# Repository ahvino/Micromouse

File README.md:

# Micromouse
Team Pizza's Micromouse
This is Team pizza's Micromouse...

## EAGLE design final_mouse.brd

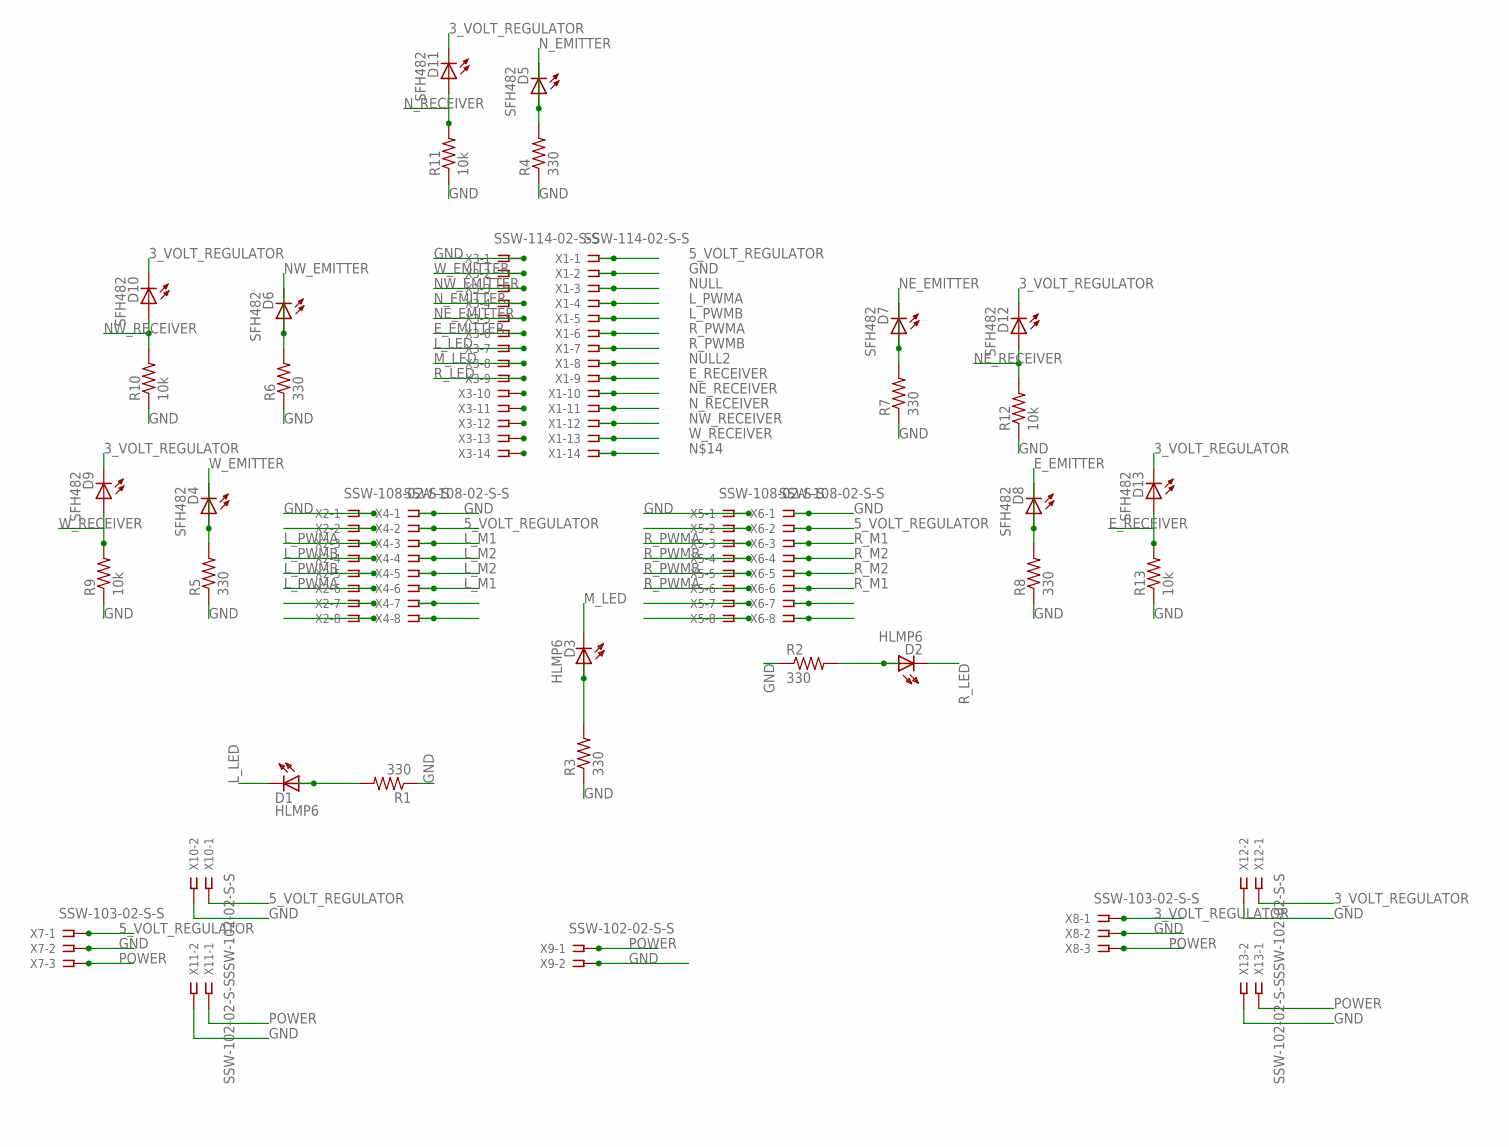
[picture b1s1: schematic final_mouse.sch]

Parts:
D1, D2, D3: HLMP6
D4, D5, D6, D7, D8, D9, D10, D11, D12, D13: SFH482
R1, R2, R3, R4, R5, R6, R7, R8: 330; 0204V
R9, R10, R11, R12, R13: 10k; 0204V
X1, X3: SSW-114-02-S-S
X2, X4, X5, X6: SSW-108-02-S-S
X7, X8: SSW-103-02-S-S
X9, X10, X11, X12, X13: SSW-102-02-S-S

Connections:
3_VOLT_REGULATOR: D9.K (C), D10.K (C), D11.K (C), D12.K (C), D13.K (C), X8.1, X12.1
5_VOLT_REGULATOR: X1.1, X4.2, X6.2, X7.1, X10.1
E_EMITTER: D8.A, D8.K (C), R8.2, X3.6
E_RECEIVER: D13.A, R13.2, X1.9
GND: R1.1, R2.1, R3.1, R4.1, R5.1, R6.1, R7.1, R8.1, R9.1, R10.1, R11.1, R12.1, R13.1, X1.2, X2.1, X3.1, X4.1, X5.1, X6.1, X7.2, X8.2, X9.2, X10.2, X11.2, X12.2, X13.2
L_LED: D1.K, X3.7
L_M1: X4.3, X4.6
L_M2: X4.4, X4.5
L_PWMA: X1.4, X2.3, X2.6
L_PWMB: X1.5, X2.4, X2.5
M_LED: D3.K, X3.8
unnamed: D1.A, R1.2
unnamed: D2.A, R2.2
unnamed: D3.A, R3.2
NE_EMITTER: D7.A, D7.K (C), R7.2, X3.5
NE_RECEIVER: D12.A, R12.2, X1.10
NULL: X1.3
NULL2: X1.8
NULL3: X2.2
NW_EMITTER: D6.A, D6.K (C), R6.2, X3.3
NW_RECEIVER: D10.A, R10.2, X1.12
N_EMITTER: D5.A, D5.K (C), R4.2, X3.4
N_RECEIVER: D11.A, R11.2, X1.11
POWER: X7.3, X8.3, X9.1, X11.1, X13.1
R_LED: D2.K, X3.9
R_M1: X6.3, X6.6
R_M2: X6.4, X6.5
R_PWMA: X1.6, X5.3, X5.6
R_PWMB: X1.7, X5.4, X5.5
W_EMITTER: D4.A, D4.K (C), R5.2, X3.2
W_RECEIVER: D9.A, R9.2, X1.13

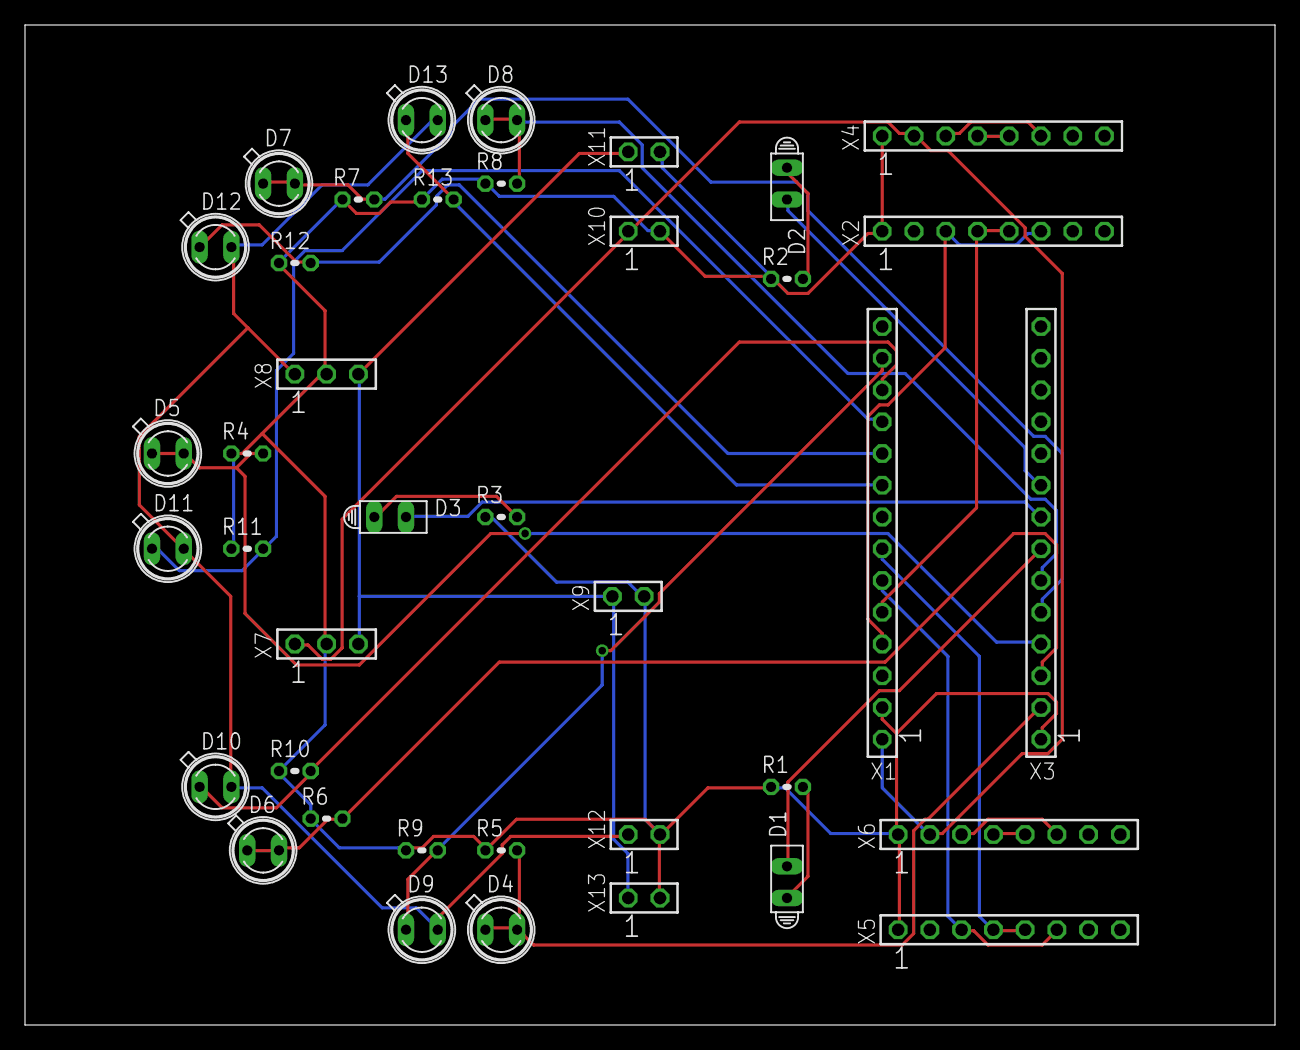
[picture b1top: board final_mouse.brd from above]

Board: 2 copper layers, 100.0 x 80.0 mm, 39 parts (0 on the bottom side), 28 nets.

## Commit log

2015-04-21 1st commit
2015-04-25 added psuedo code
2015-08-19 updated micromouse
2015-08-19 updates with schematic
2015-08-19 with sch and brd
